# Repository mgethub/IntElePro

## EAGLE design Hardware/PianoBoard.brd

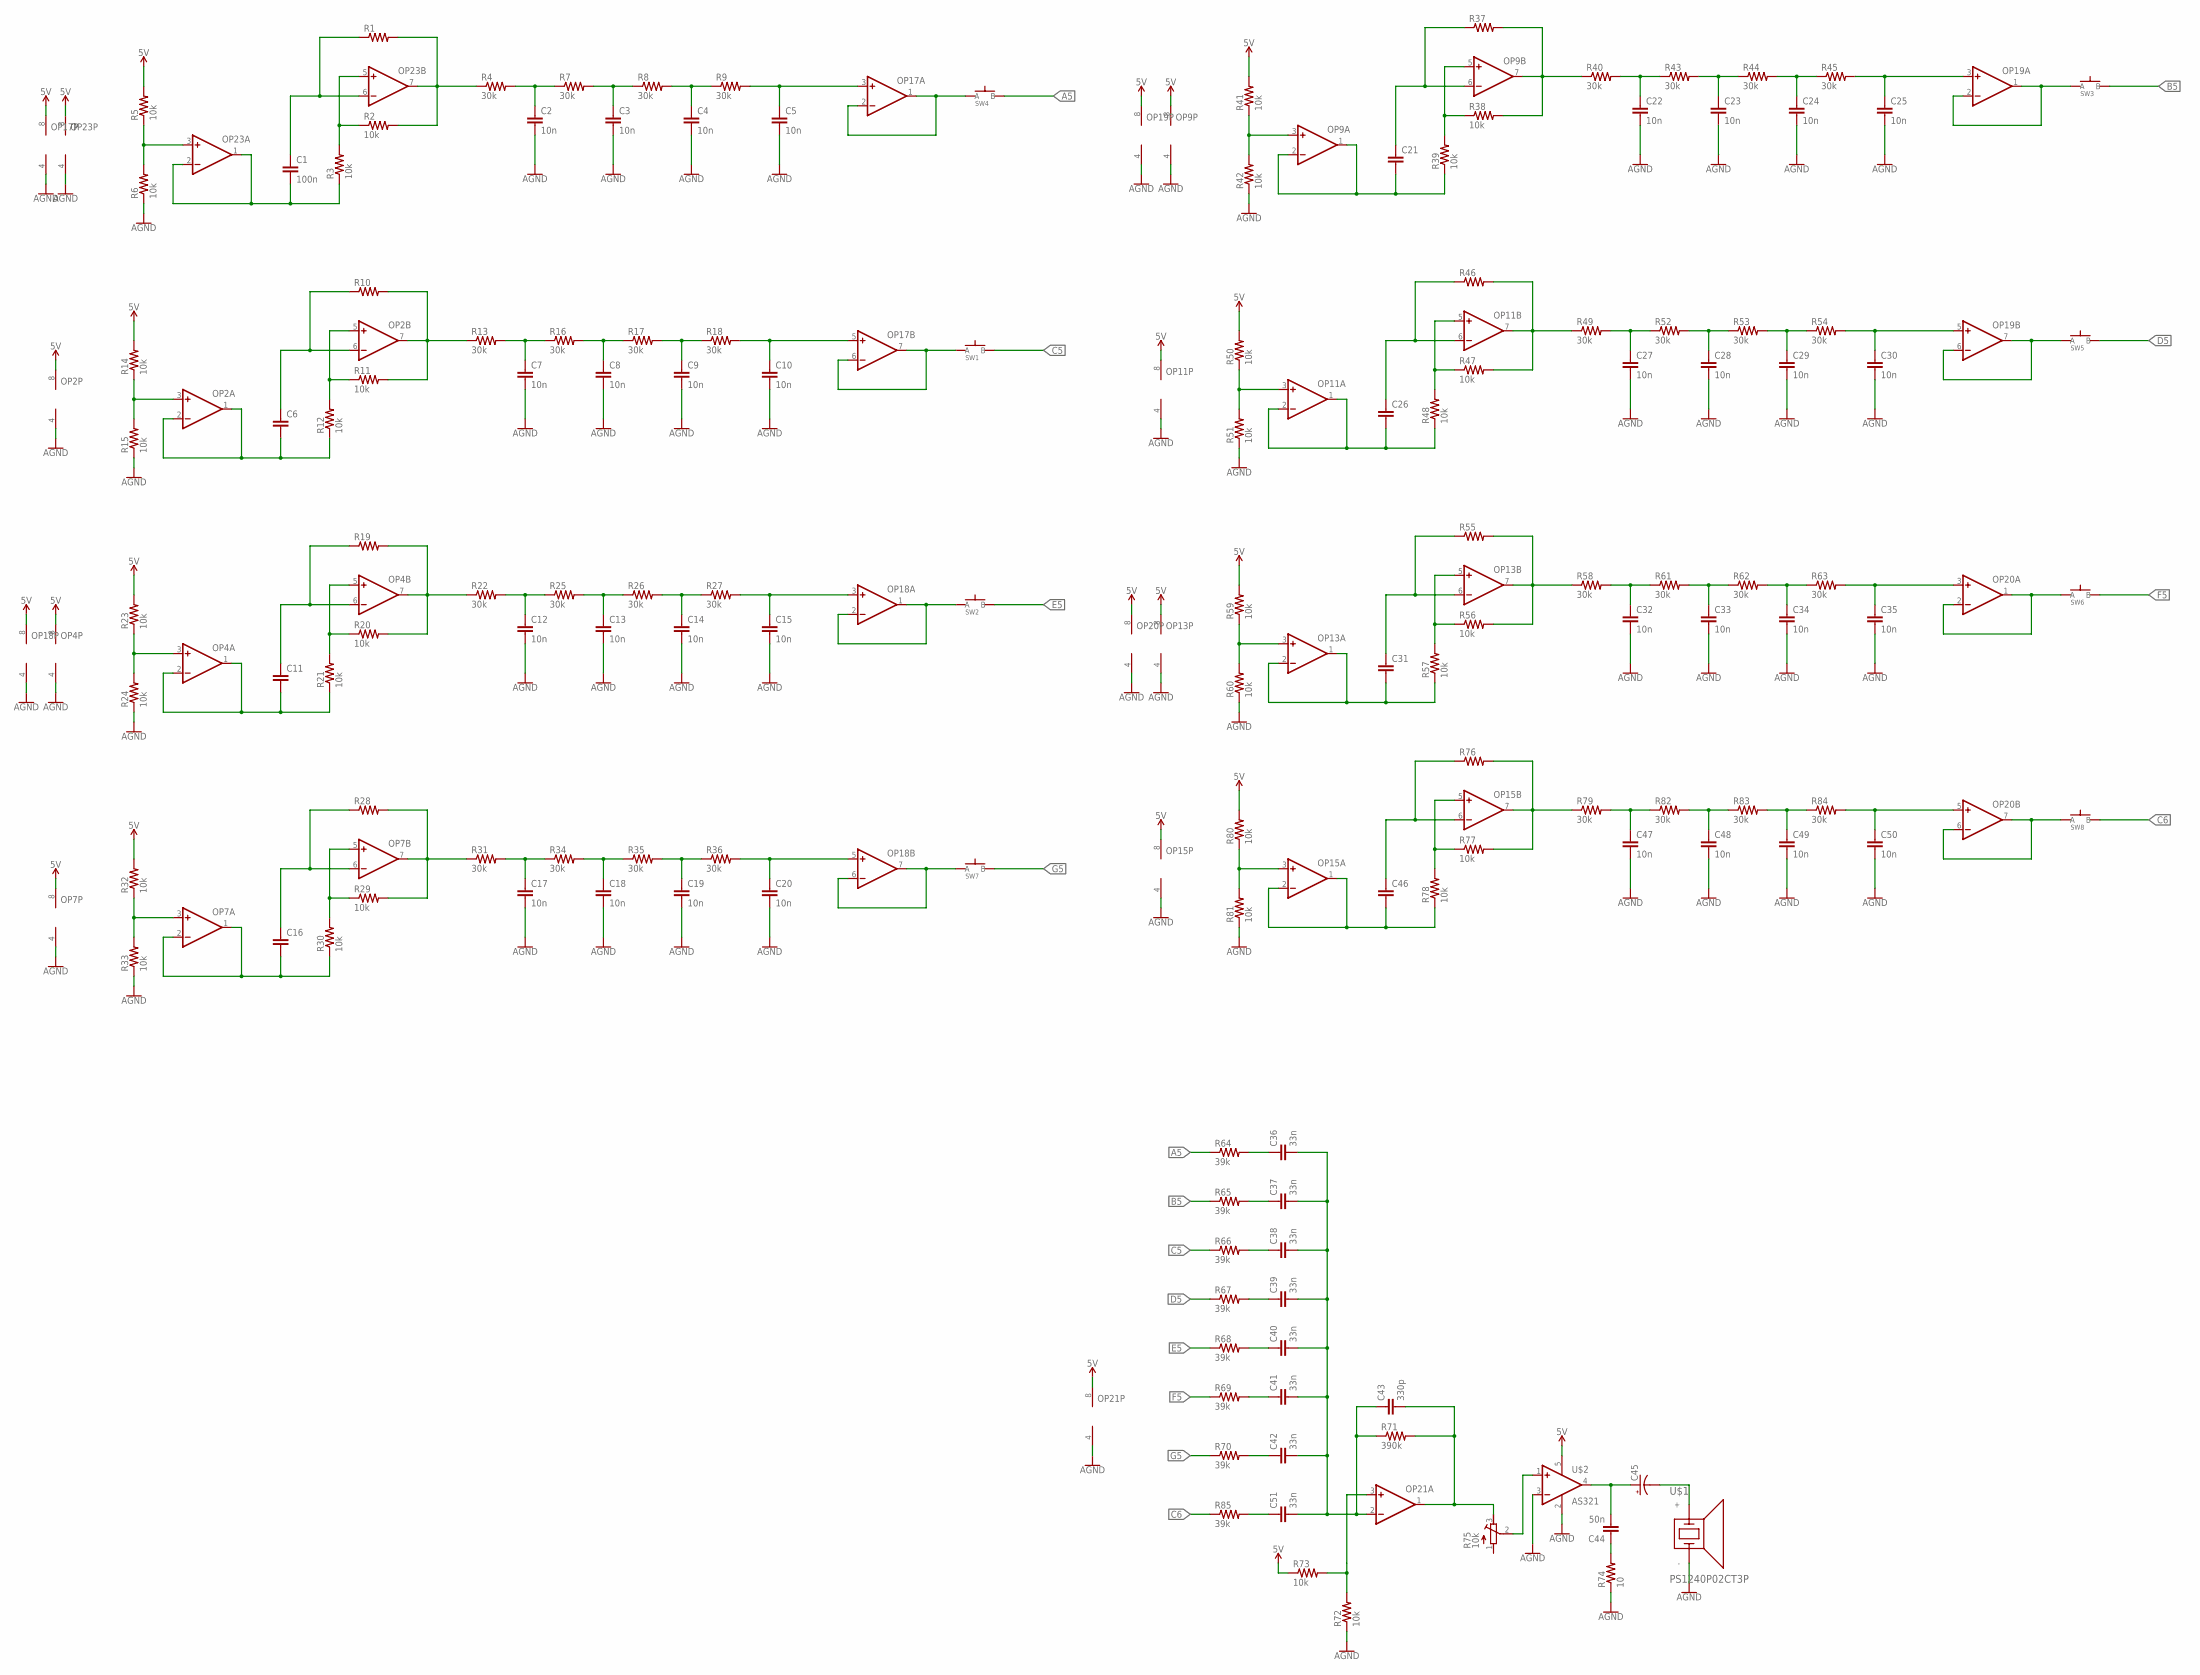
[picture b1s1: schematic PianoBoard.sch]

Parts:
C1: 100n; C0603
C2, C3, C4, C5, C7, C8, C9, C10, C12, C13, C14, C15, C17, C18, C19, C20, C22, C23, C24, C25, C27, C28, C29, C30, C32, C33, C34, C35, C47, C48, C49, C50: 10n; C0603
C6, C11, C16, C21, C26, C31, C46: CAPACITOR0603; C0603
C36, C37, C38, C39, C40, C41, C42, C51: 33n; C0603
C43: 330p; C0603
C44: 50n; C0603
C45: CAPACITOR.POLAR.0603; C0603.POLAR
OP2, OP4, OP7, OP9, OP11, OP13, OP15, OP23: OP-DUALR; SO8
OP17, OP18, OP19, OP20, OP21: OP-DUALMCP6002R; SO8
R1, R10, R19, R28, R37, R46, R55, R76: RESISTOR0603; R0603
R2, R3, R5, R6, R11, R12, R14, R15, R20, R21, R23, R24, R29, R30, R32, R33, R38, R39, R41, R42, R47, R48, R50, R51, R56, R57, R59, R60, R72, R73, R77, R78, R80, R81: 10k; R0603
R4, R7, R8, R9, R13, R16, R17, R18, R22, R25, R26, R27, R31, R34, R35, R36, R40, R43, R44, R45, R49, R52, R53, R54, R58, R61, R62, R63, R79, R82, R83, R84: 30k; R0603
R64, R65, R66, R67, R68, R69, R70, R85: 39k; R0603
R71: 390k; R0603
R74: 10; R0603
R75: 10k; 16MMROTARYPOT
SW1, SW2, SW3, SW4, SW5, SW6, SW7, SW8: SPST.KT11P4SM34LFS
U$1: PS1240P02CT3P; PIEZO-1
U$2: AS321; SOT23-5

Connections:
5V: OP2.8 (V+), OP4.8 (V+), OP7.8 (V+), OP9.8 (V+), OP11.8 (V+), OP13.8 (V+), OP15.8 (V+), OP17.8 (V+), OP18.8 (V+), OP19.8 (V+), OP20.8 (V+), OP21.8 (V+), OP23.8 (V+), R5.2, R14.2, R23.2, R32.2, R41.2, R50.2, R59.2, R73.1, R80.2, U$2.5 (V+)
A5: R64.1, SW4.3 (B), SW4.4 (B)
AGND: C2.2, C3.2, C4.2, C5.2, C7.2, C8.2, C9.2, C10.2, C12.2, C13.2, C14.2, C15.2, C17.2, C18.2, C19.2, C20.2, C22.2, C23.2, C24.2, C25.2, C27.2, C28.2, C29.2, C30.2, C32.2, C33.2, C34.2, C35.2, C47.2, C48.2, C49.2, C50.2, OP2.4 (V-), OP4.4 (V-), OP7.4 (V-), OP9.4 (V-), OP11.4 (V-), OP13.4 (V-), OP15.4 (V-), OP17.4 (V-), OP18.4 (V-), OP19.4 (V-), OP20.4 (V-), OP21.4 (V-), OP23.4 (V-), R6.1, R15.1, R24.1, R33.1, R42.1, R51.1, R60.1, R72.1, R74.1, R81.1, U$1.-, U$2.2 (V-), U$2.3 (-IN)
B5: R65.1, SW3.3 (B), SW3.4 (B)
C5: R66.1, SW1.3 (B), SW1.4 (B)
C6: R85.1, SW8.3 (B), SW8.4 (B)
D5: R67.1, SW5.3 (B), SW5.4 (B)
E5: R68.1, SW2.3 (B), SW2.4 (B)
F5: R69.1, SW6.3 (B), SW6.4 (B)
G5: R70.1, SW7.3 (B), SW7.4 (B)
unnamed: OP23.3 (+IN), R5.1, R6.2
unnamed: C1.2, OP23.1 (OUT), OP23.2 (-IN), R3.1
unnamed: OP23.5 (+IN), R2.1, R3.2
unnamed: OP2.3 (+IN), R14.1, R15.2
unnamed: C2.1, R4.2, R7.1
unnamed: OP23.7 (OUT), R1.2, R2.2, R4.1
unnamed: C3.1, R7.2, R8.1
unnamed: C4.1, R8.2, R9.1
unnamed: C5.1, OP17.3 (+IN), R9.2
unnamed: OP17.1 (OUT), OP17.2 (-IN), SW4.1 (A), SW4.2 (A)
unnamed: C6.2, OP2.1 (OUT), OP2.2 (-IN), R12.1
unnamed: OP2.5 (+IN), R11.1, R12.2
unnamed: OP2.7 (OUT), R10.2, R11.2, R13.1
unnamed: C7.1, R13.2, R16.1
unnamed: C8.1, R16.2, R17.1
unnamed: C9.1, R17.2, R18.1
unnamed: C10.1, OP17.5 (+IN), R18.2
unnamed: OP17.6 (-IN), OP17.7 (OUT), SW1.1 (A), SW1.2 (A)
unnamed: C6.1, OP2.6 (-IN), R10.1
unnamed: OP4.3 (+IN), R23.1, R24.2
unnamed: C11.2, OP4.1 (OUT), OP4.2 (-IN), R21.1
unnamed: OP4.5 (+IN), R20.1, R21.2
unnamed: OP4.7 (OUT), R19.2, R20.2, R22.1
unnamed: C12.1, R22.2, R25.1
unnamed: C13.1, R25.2, R26.1
unnamed: C14.1, R26.2, R27.1
unnamed: C15.1, OP18.3 (+IN), R27.2
unnamed: OP18.1 (OUT), OP18.2 (-IN), SW2.1 (A), SW2.2 (A)
unnamed: C11.1, OP4.6 (-IN), R19.1
unnamed: OP7.3 (+IN), R32.1, R33.2
unnamed: C1.1, OP23.6 (-IN), R1.1
unnamed: C16.2, OP7.1 (OUT), OP7.2 (-IN), R30.1
unnamed: OP7.5 (+IN), R29.1, R30.2
unnamed: OP7.7 (OUT), R28.2, R29.2, R31.1
unnamed: C17.1, R31.2, R34.1
unnamed: C18.1, R34.2, R35.1
unnamed: C19.1, R35.2, R36.1
unnamed: C20.1, OP18.5 (+IN), R36.2
unnamed: OP18.6 (-IN), OP18.7 (OUT), SW7.1 (A), SW7.2 (A)
unnamed: C16.1, OP7.6 (-IN), R28.1
unnamed: OP9.3 (+IN), R41.1, R42.2
unnamed: C21.2, OP9.1 (OUT), OP9.2 (-IN), R39.1
unnamed: OP9.5 (+IN), R38.1, R39.2
unnamed: OP9.7 (OUT), R37.2, R38.2, R40.1
unnamed: C22.1, R40.2, R43.1
unnamed: C23.1, R43.2, R44.1
unnamed: C24.1, R44.2, R45.1
unnamed: C25.1, OP19.3 (+IN), R45.2
unnamed: OP19.1 (OUT), OP19.2 (-IN), SW3.1 (A), SW3.2 (A)
unnamed: C21.1, OP9.6 (-IN), R37.1
unnamed: OP11.3 (+IN), R50.1, R51.2
unnamed: C26.2, OP11.1 (OUT), OP11.2 (-IN), R48.1
unnamed: OP11.5 (+IN), R47.1, R48.2
unnamed: OP11.7 (OUT), R46.2, R47.2, R49.1
unnamed: C27.1, R49.2, R52.1
unnamed: C28.1, R52.2, R53.1
unnamed: C29.1, R53.2, R54.1
unnamed: C30.1, OP19.5 (+IN), R54.2
unnamed: OP19.6 (-IN), OP19.7 (OUT), SW5.1 (A), SW5.2 (A)
unnamed: C26.1, OP11.6 (-IN), R46.1
unnamed: OP13.3 (+IN), R59.1, R60.2
unnamed: C31.2, OP13.1 (OUT), OP13.2 (-IN), R57.1
unnamed: OP13.5 (+IN), R56.1, R57.2
unnamed: OP13.7 (OUT), R55.2, R56.2, R58.1
unnamed: C32.1, R58.2, R61.1
unnamed: C33.1, R61.2, R62.1
unnamed: C34.1, R62.2, R63.1
unnamed: C35.1, OP20.3 (+IN), R63.2
unnamed: OP20.1 (OUT), OP20.2 (-IN), SW6.1 (A), SW6.2 (A)
unnamed: C31.1, OP13.6 (-IN), R55.1
unnamed: C36.1, R64.2
unnamed: C37.1, R65.2
unnamed: C38.1, R66.2
unnamed: C39.1, R67.2
unnamed: C40.1, R68.2
unnamed: C41.1, R69.2
unnamed: C42.1, R70.2
unnamed: C43.2, OP21.1 (OUT), R71.2, R75.3 (E)
unnamed: R72.2, R73.2
unnamed: R75.2 (S), U$2.1 (+IN)
unnamed: C44.2, C45.A (+), U$2.4 (OUT)
unnamed: C44.1, R74.2
unnamed: C45.C (-), U$1.+
unnamed: OP15.3 (+IN), R80.1, R81.2
unnamed: C46.2, OP15.1 (OUT), OP15.2 (-IN), R78.1
unnamed: OP15.5 (+IN), R77.1, R78.2
unnamed: OP15.7 (OUT), R76.2, R77.2, R79.1
unnamed: C47.1, R79.2, R82.1
unnamed: C48.1, R82.2, R83.1
unnamed: C49.1, R83.2, R84.1
unnamed: C50.1, OP20.5 (+IN), R84.2
unnamed: OP20.6 (-IN), OP20.7 (OUT), SW8.1 (A), SW8.2 (A)
unnamed: C46.1, OP15.6 (-IN), R76.1
unnamed: C51.1, R85.2
unnamed: C36.2, C37.2, C38.2, C39.2, C40.2, C41.2, C42.2, C43.1, C51.2, OP21.2 (-IN), R71.1

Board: 2 copper layers, 159 parts (0 on the bottom side), 105 nets, no tracks yet.

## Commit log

2021-02-20 adding project test docs
2021-03-13 forgot to add edits
2021-03-27 first board design
2021-03-27 placement update
